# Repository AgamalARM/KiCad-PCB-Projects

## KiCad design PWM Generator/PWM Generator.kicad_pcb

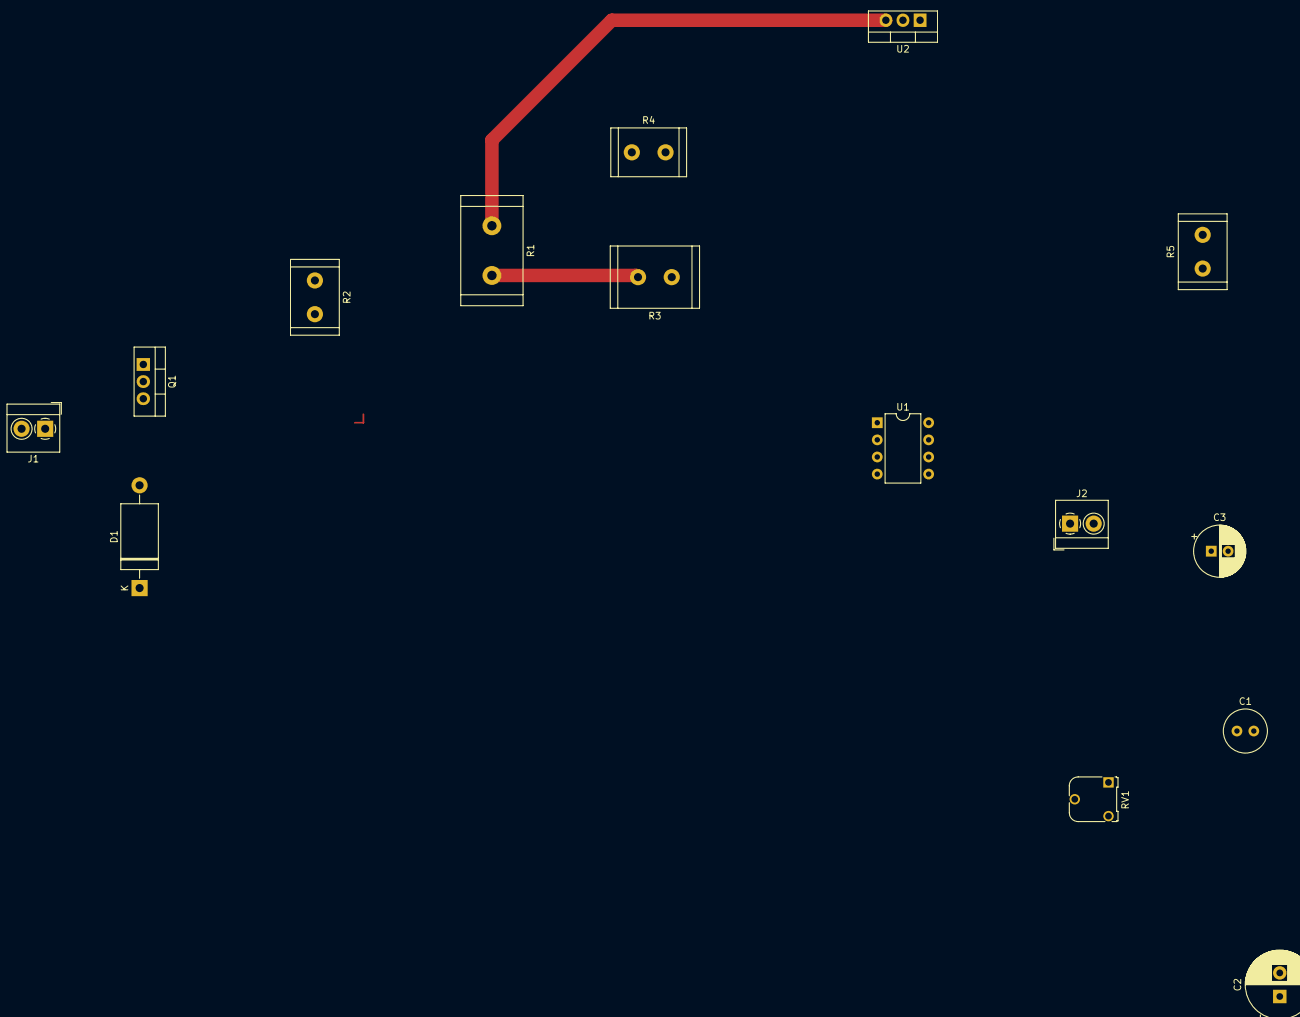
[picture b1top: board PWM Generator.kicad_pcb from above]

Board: 2 copper layers, 15 parts (0 on the bottom side), 10 nets.

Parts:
C1: C; C_Radial_D6.3mm_H5.0mm_P2.50mm
C2: CP1; CP_Radial_D10.0mm_P3.50mm
C3: CP1; CP_Radial_D7.5mm_P2.50mm
D1: D; D_DO-27_P15.24mm_Horizontal
J1, J2: Screw_Terminal_01x02; TerminalBlock_4Ucon_1x02_P3.50mm_Horizontal
Q1: IRF3205; TO-220-3_Vertical
R1: R; R_Radial_Power_L16.1mm_W9.0mm_P7.37mm
R2, R4, R5: R; R_Radial_Power_L11.0mm_W7.0mm_P5.00mm
R3: R; R_Radial_Power_L13.0mm_W9.0mm_P5.00mm
RV1: R_POT; Potentiometer_Runtron_RM-065_Vertical
U1: LM358; DIP-8_W7.62mm
U2: LM7805_TO220; TO-220-3_Vertical

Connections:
+5V: C3.1, R1.1, RV1.1, U1.8, U2.3
+12C: C2.1, D1.1, J1.2, J2.1, U2.1
GND: C1.2, C2.2, C3.2, J1.1, Q1.3, R2.2, RV1.3, U1.4, U2.2
unnamed: C1.1, R4.2, U1.2, U1.5
unnamed: D1.2, J2.2, Q1.2
unnamed: Q1.1, R5.2
unnamed: R1.2, R2.1, R3.2, U1.3
unnamed: R3.1, R4.1, U1.1
unnamed: R5.1, U1.7
unnamed: RV1.2, U1.6
